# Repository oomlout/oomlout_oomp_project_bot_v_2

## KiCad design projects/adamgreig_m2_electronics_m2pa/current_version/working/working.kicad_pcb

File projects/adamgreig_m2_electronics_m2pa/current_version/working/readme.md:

# m2_electronics
 
## summary 
* id: adamgreig_m2_electronics_m2pa
* user: adamgreig
* name: m2_electronics
* board: m2pa
* repo: https://github.com/adamgreig/m2-electronics
* src_file_repo_kicad_pcb: m2pa/m2pa-instrument.kicad_pcb
* src_file_repo_kicad_pcb_link: https://github.com/adamgreig/m2-electronics/tree/master/m2pa/m2pa-instrument.kicad_pcb

* src_file_repo_sch: 
* src_file_repo_sch_link: https://github.com/adamgreig/m2-electronics/tree/master/
* full details link: https://github.com/oomlout/oomlout_oomp_project_bot_v_2/tree/main/projects/adamgreig_m2_electronics_m2pa/current_version/working  

## pcb  

[board (pdf)](working.pdf)  

## working_bom
| Id | Designator | Footprint | Quantity | Designation | Supplier and ref |  | None | 
| --- | --- | --- | --- | --- | --- | --- | --- | 
| 1 | C1 | C0402 | 1 | 10p |  |  | [''] | 
| 2 | C2,C7 | C0402 | 2 | 20p |  |  | [''] | 
| 3 | C3 | C0402 | 1 | 100p |  |  | [''] | 
| 4 | C4 | C0603 | 1 | 10n |  |  | [''] | 
| 5 | C5 | C0402 | 1 | 6p2 |  |  | [''] | 
| 6 | C6 | C1206 | 1 | 10Âµ |  |  | [''] | 
| 7 | D1,D2,D3 | R0402 | 3 | CGA0402MLC-12G |  |  | [''] | 
| 8 | IC1 | SOT89-3 | 1 | ADL5324 |  |  | [''] | 
| 9 | L1 | L0603 | 1 | 1n6 |  |  | [''] | 
| 10 | L2 | L0603 | 1 | 120n |  |  | [''] | 
| 11 | L3 | L0402 | 1 | 5n6 |  |  | [''] | 
| 12 | P1 | S02B-PASK-2 | 1 | CONN_01X02 |  |  | [''] | 
| 13 | P2,P3 | SMA-142-0701-801 | 2 | SMA |  |  | [''] | 
| 14 | R1 | R0402 | 1 | 2 |  |  | [''] | 
| 15 | G*** | cusf_logo_small | 1 | LOGO |  |  | [''] | 
| 16 | G*** | cusf_logo_full | 1 | LOGO |  |  | [''] |

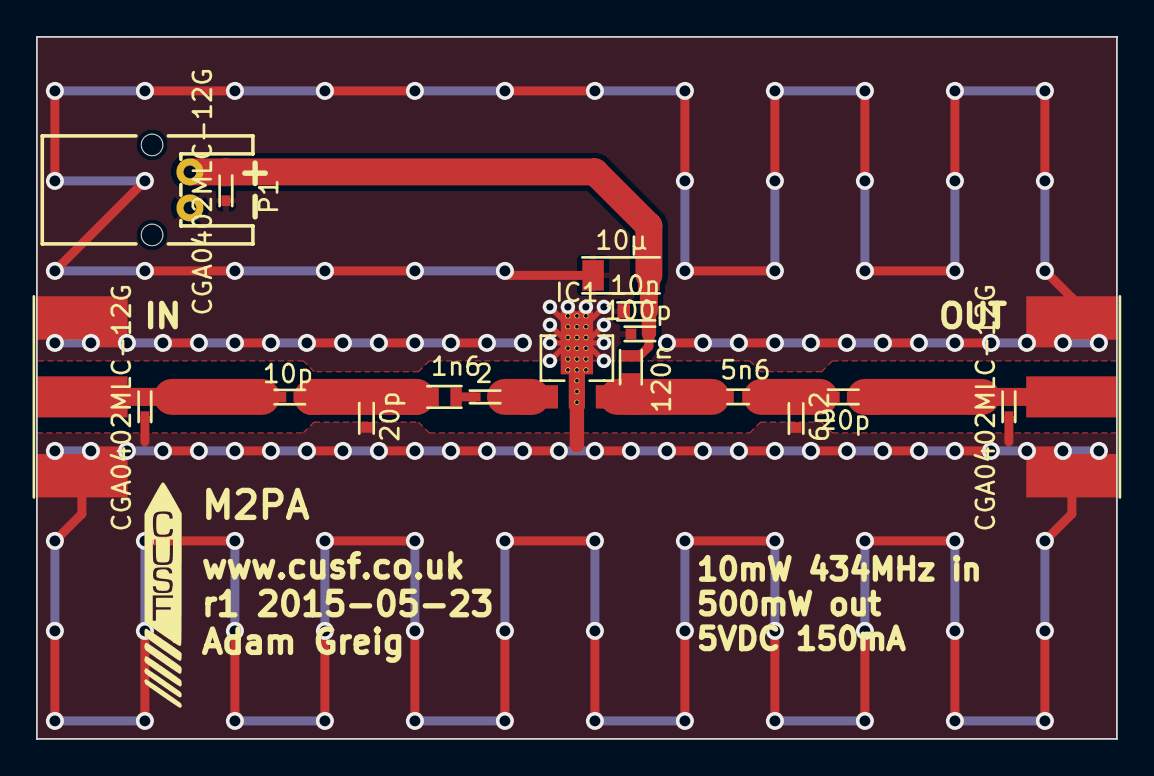
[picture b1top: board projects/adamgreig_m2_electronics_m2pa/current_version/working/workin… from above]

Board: 2 copper layers, 60.0 x 39.0 mm, 18 parts (0 on the bottom side), 9 nets.

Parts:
C1: 10p; C0402
C2, C7: 20p; C0402
C3: 100p; C0402
C4: 10n; C0603
C5: 6p2; C0402
C6: 10µ; C1206
D1, D2, D3: CGA0402MLC-12G; R0402
IC1: ADL5324; SOT89-3
L1: 1n6; L0603
L2: 120n; L0603
L3: 5n6; L0402
P1: CONN_01X02; S02B-PASK-2
P2, P3: SMA; SMA-142-0701-801
R1: 2; R0402

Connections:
+5V: C3.1, C4.1, C6.1, D3.1, L2.2, P1.2
GND: C2.1, C3.2, C4.2, C5.1, C6.2, D1.2, D2.2, D3.2, IC1.2, P1.1, P2.2, P2.3, P2.4, P2.5, P3.2, P3.3, P3.4, P3.5
unnamed: C1.1, C2.2, L1.2
unnamed: C1.2, D1.1, P2.1
unnamed: C5.2, C7.1, L3.1
unnamed: C7.2, D2.1, P3.1
unnamed: IC1.1, R1.1
unnamed: IC1.3, L2.1, L3.2
unnamed: L1.1, R1.2

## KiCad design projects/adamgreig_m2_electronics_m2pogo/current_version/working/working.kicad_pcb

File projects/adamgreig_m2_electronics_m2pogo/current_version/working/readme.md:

# m2_electronics
 
## summary 
* id: adamgreig_m2_electronics_m2pogo
* user: adamgreig
* name: m2_electronics
* board: m2pogo
* repo: https://github.com/adamgreig/m2-electronics
* src_file_repo_kicad_pcb: m2pogo/m2pogo.kicad_pcb
* src_file_repo_kicad_pcb_link: https://github.com/adamgreig/m2-electronics/tree/master/m2pogo/m2pogo.kicad_pcb

* src_file_repo_sch: m2pogo/m2pogo.sch
* src_file_repo_sch_link: https://github.com/adamgreig/m2-electronics/tree/master/m2pogo/m2pogo.sch
* full details link: https://github.com/oomlout/oomlout_oomp_project_bot_v_2/tree/main/projects/adamgreig_m2_electronics_m2pogo/current_version/working  

## schematic  
  
[schematic (pdf)](working_schematic.pdf) 

## pcb  

[board (pdf)](working.pdf)  

## working_bom
| Id | Designator | Footprint | Quantity | Designation | Supplier and ref |  | None | 
| --- | --- | --- | --- | --- | --- | --- | --- | 
| 1 | P3,P4,P5,P6 | POGO | 4 | CONN_1 |  |  | [''] | 
| 2 | P1,P2 | S02B-PASK-2 | 2 | CONN_2 |  |  | [''] | 
| 3 | X4,X3 | M3_MOUNT | 2 | MOUNT |  |  | [''] | 

## bom_schematic
| Ref | Qnty | Value | Cmp name | Footprint | Description | Vendor | DNP | 
| --- | --- | --- | --- | --- | --- | --- | --- | 
| P1, P2 | 2 | CONN_2 | CONN_2 | m2pogo:S02B-PASK-2 |  |  |  | 
| P3, P4, P5, P6 | 4 | CONN_1 | CONN_1 | m2pogo:POGO |  |  |  | 
| X1, X2 | 2 | HOUSING | PART |  |  |  |  | 
| X3, X4 | 2 | MOUNT | PART | m2pogo:M3_MOUNT |  |  |  |

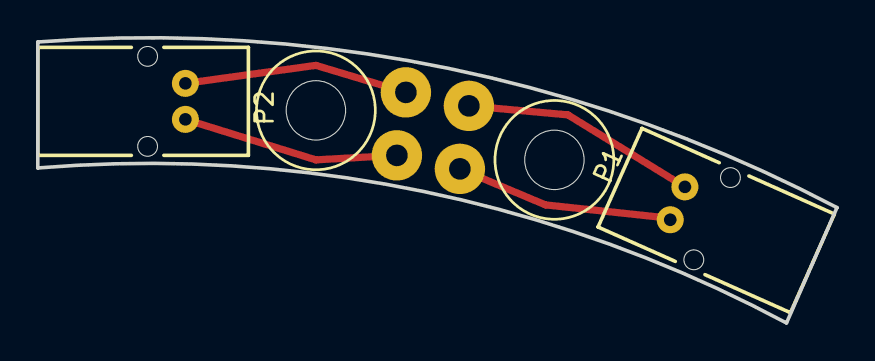
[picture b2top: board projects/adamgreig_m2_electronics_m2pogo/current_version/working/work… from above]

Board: 2 copper layers, 44.4 x 15.8 mm, 8 parts (0 on the bottom side), 4 nets.

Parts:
P1, P2: CONN_2; S02B-PASK-2
P3, P4, P5, P6: CONN_1; POGO
X3, X4: MOUNT; M3_MOUNT

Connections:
unnamed: P1.1, P4.1
unnamed: P1.2, P3.1
unnamed: P2.1, P6.1
unnamed: P2.2, P5.1

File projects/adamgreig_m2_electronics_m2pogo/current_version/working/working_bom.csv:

"Id";"Designator";"Footprint";"Quantity";"Designation";"Supplier and ref";
1;"P3,P4,P5,P6";"POGO";4;"CONN_1";;;
2;"P1,P2";"S02B-PASK-2";2;"CONN_2";;;
3;"X4,X3";"M3_MOUNT";2;"MOUNT";;;

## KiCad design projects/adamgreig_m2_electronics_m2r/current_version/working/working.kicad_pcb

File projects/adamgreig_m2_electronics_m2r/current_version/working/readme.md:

# m2_electronics
 
## summary 
* id: adamgreig_m2_electronics_m2r
* user: adamgreig
* name: m2_electronics
* board: m2r
* repo: https://github.com/adamgreig/m2-electronics
* src_file_repo_kicad_pcb: m2r/pcb_r2/m2r.kicad_pcb
* src_file_repo_kicad_pcb_link: https://github.com/adamgreig/m2-electronics/tree/master/m2r/pcb_r2/m2r.kicad_pcb

* src_file_repo_sch: m2r/pcb_r2/m2r.sch
* src_file_repo_sch_link: https://github.com/adamgreig/m2-electronics/tree/master/m2r/pcb_r2/m2r.sch
* full details link: https://github.com/oomlout/oomlout_oomp_project_bot_v_2/tree/main/projects/adamgreig_m2_electronics_m2r/current_version/working  

## pcb  

[board (pdf)](working.pdf)  

## working_bom
| Id | Designator | Footprint | Quantity | Designation | Supplier and ref |  | None | 
| --- | --- | --- | --- | --- | --- | --- | --- | 
| 1 | C1,C2,C3,C4,C5,C6,C11,C14,C15,C24,C25,C26,C27,C29,C30,C34 | C0603 | 16 | 100n |  |  | [''] | 
| 2 | C7,C8,C9,C10,C13 | C0603 | 5 | 2Âµ2 |  |  | [''] | 
| 3 | C12 | C0603 | 1 | 1n |  |  | [''] | 
| 4 | C23 | C0603 | 1 | 10Âµ |  |  | [''] | 
| 5 | C28 | C0603 | 1 | 1Âµ |  |  | [''] | 
| 6 | C35,C36 | C0603 | 2 | 15p |  |  | [''] | 
| 7 | D1,D2 | LED0603 | 2 | GRN |  |  | [''] | 
| 8 | D3,D4,D5,D6 | LED0603 | 4 | YELLOW |  |  | [''] | 
| 9 | D7,D8,D9,D10,D11,D12,D13 | R0402 | 7 | CGA0402MLC-12G |  |  | [''] | 
| 10 | IC1 | SOT223 | 1 | ADP3338 |  |  | [''] | 
| 11 | IC2 | MSOP8 | 1 | ADP3335 |  |  | [''] | 
| 12 | IC3,IC4,IC5 | SOIC8 | 3 | ADuM1201 |  |  | [''] | 
| 13 | IC6 | MTX2 | 1 | MTX2 |  |  | [''] | 
| 14 | IC8 | MAX-7Q | 1 | MAX-7Q |  |  | [''] | 
| 15 | IC10 | LQFP48 | 1 | STM32F303C |  |  | [''] | 
| 16 | P1,P8,P9 | S02B-PASK-2 | 3 | CONN_2 |  |  | [''] | 
| 17 | P2,P7 | SMA-142-0701-801 | 2 | SMA |  |  | [''] | 
| 18 | P3,P4,P5 | S04B-PASK-2 | 3 | CONN_4 |  |  | [''] | 
| 19 | P6 | FTSH-105-01-F-D-K | 1 | SWD |  |  | [''] | 
| 20 | Q1 | SOT-23 | 1 | Q_PMOS_GSD_PSV |  |  | [''] | 
| 21 | Q2 | SOT-23 | 1 | Q_NMOS_GSD_PSV |  |  | [''] | 
| 22 | R1,R3 | R0603 | 2 | 10k |  |  | [''] | 
| 23 | R2 | R0603 | 1 | 1k |  |  | [''] | 
| 24 | R4,R5,R7,R8,R9,R10,R11,R12,R13,R14,R15,R16 | R0603 | 12 | 100 |  |  | [''] | 
| 25 | R6 | R0603 | 1 | 10 |  |  | [''] | 
| 26 | SP1 | ABI-042-RC | 1 | SPEAKER |  |  | [''] | 
| 27 | TP1,TP2,TP4,TP7,TP11,TP12,TP13,TP14,TP15,TP16,TP17,TP18,TP19,TP20,TP21,TP22,TP23,TP24,TP25,TP26,TP27,TP28,TP29 | TESTPAD | 23 | TESTPAD |  |  | [''] | 
| 28 | X10 | XTAL50x32 | 1 | 8M |  |  | [''] | 
| 29 | X11,X12,X13,X14 | M3_MOUNT | 4 | M3 MOUNT |  |  | [''] | 
| 30 | G*** | cusf_logo_small | 1 | LOGO |  |  | [''] | 
| 31 | G*** | cusf_logo_full | 1 | LOGO |  |  | [''] |

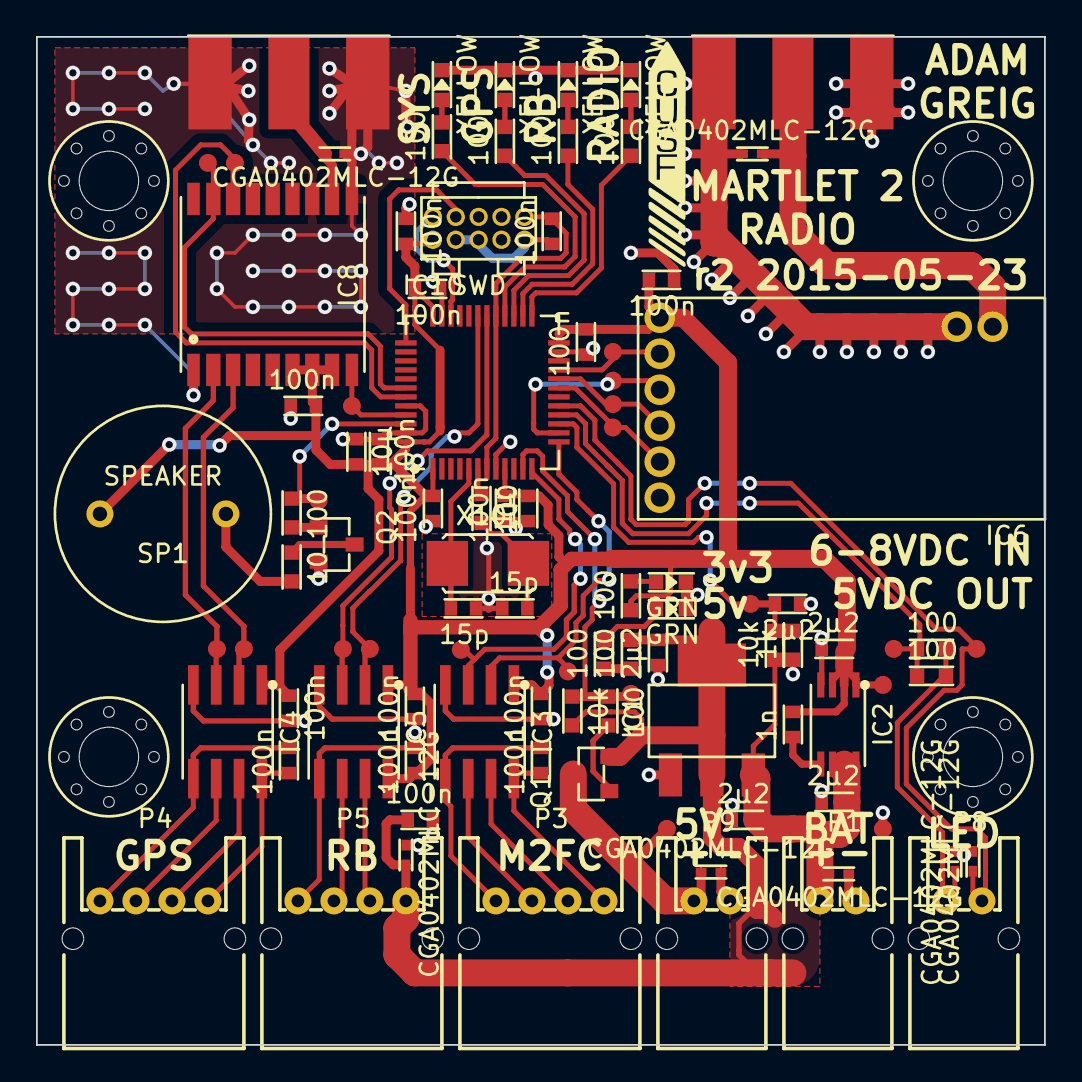
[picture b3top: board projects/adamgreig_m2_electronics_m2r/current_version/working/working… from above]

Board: 2 copper layers, 56.0 x 56.0 mm, 103 parts (0 on the bottom side), 58 nets.

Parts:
C1, C2, C3, C4, C5, C6, C11, C14, C15, C24, C25, C26, C27, C29, C30, C34: 100n; C0603
C7, C8, C9, C10, C13: 2µ2; C0603
C12: 1n; C0603
C23: 10µ; C0603
C28: 1µ; C0603
C35, C36: 15p; C0603
D1, D2: GRN; LED0603
D3, D4, D5, D6: YELLOW; LED0603
D7, D8, D9, D10, D11, D12, D13: CGA0402MLC-12G; R0402
IC1: ADP3338; SOT223
IC2: ADP3335; MSOP8
IC3, IC4, IC5: ADuM1201; SOIC8
IC6: MTX2
IC8: MAX-7Q
IC10: STM32F303C; LQFP48
P1, P8, P9: CONN_2; S02B-PASK-2
P2, P7: SMA; SMA-142-0701-801
P3, P4, P5: CONN_4; S04B-PASK-2
P6: SWD; FTSH-105-01-F-D-K
Q1: Q_PMOS_GSD_PSV; SOT-23
Q2: Q_NMOS_GSD_PSV; SOT-23
R1, R3: 10k; R0603
R2: 1k; R0603
R4, R5, R7, R8, R9, R10, R11, R12, R13, R14, R15, R16: 100; R0603
R6: 10; R0603
SP1: SPEAKER; ABI-042-RC
TP1, TP2, TP4, TP7, TP11, TP12, TP13, TP14, TP15, TP16, TP17, TP18, TP19, TP20, TP21, TP22, TP23, TP24, TP25, TP26, TP27, TP28, TP29: TESTPAD
X10: 8M; XTAL50x32
X11, X12, X13, X14: M3 MOUNT; M3_MOUNT

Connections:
5V_OUT: IC10.11, R3.2, R16.2, TP27.1
+3V3: C3.2, C5.2, C6.1, C8.1, C11.1, C12.1, C14.1, C15.1, C23.1, C24.1, C25.1, C26.1, C27.1, C28.1, C29.1, C30.1, IC2.1, IC2.2, IC2.3, IC3.1, IC4.1, IC5.1, IC5.8, IC6.3, IC8.6, IC8.7, IC8.8, IC10.1, IC10.9, IC10.24, IC10.36, IC10.48, P6.1, R8.2, SP1.1, TP1.1
+5V: C4.2, C10.1, D7.1, IC1.2, P5.1, Q1.2, R3.1, R9.1, TP2.1
+BATT: C7.1, C9.1, D8.1, IC1.3, IC2.6, IC2.7, IC2.8, P1.2, R1.2, TP11.1
BAT_MON: C13.1, IC10.15, R1.1, R2.1, TP13.1
BUZZER: IC10.46, R15.2, TP28.1
GND: C3.1, C4.1, C5.1, C6.2, C7.2, C8.2, C9.2, C10.2, C11.2, C13.2, C14.2, C15.2, C23.2, C24.2, C25.2, C26.2, C27.2, C28.2, C29.2, C30.2, C34.2, C35.2, C36.2, D1.2, D2.2, D3.2, D4.2, D5.2, D6.2, D7.2, D8.2, D9.2, D10.1, D11.1, D12.2, D13.1, IC1.1, IC2.4, IC3.4, IC4.4, IC5.4, IC5.5, IC6.2, IC6.8, IC8.1, IC8.10, IC8.12, IC10.8, IC10.23, IC10.35, IC10.44, IC10.47, P1.1, P2.2, P2.3, P2.4, P2.5, P5.4, P6.3, P6.5, P6.9, P7.2, P7.3, P7.4, P7.5, P9.1, Q2.2, R2.2, TP12.1
GPS_RESET: IC8.9, IC10.45, TP19.1
GPS_RX: IC4.2, IC8.3, TP4.1
GPS_SCL: IC8.17, IC10.42, TP20.1
GPS_SDA: IC8.16, IC10.43, TP21.1
GPS_TX: IC4.3, IC8.2, TP7.1
LED_1: IC10.25, R10.2
LED_2: IC10.26, R12.2
LED_3: IC10.27, R11.2
LED_4: IC10.28, R13.2
LED_A: IC10.16, R4.2, R5.2, TP18.1
LED_C: D11.2, IC10.17, P8.1, TP26.1
NTX2B_EN: IC6.4, IC10.21, TP22.1
NTX2B_P0: IC6.7, IC10.19, TP25.1
NTX2B_P1: IC6.6, IC10.20, TP24.1
NTX2B_TXD: IC6.5, IC10.14, TP23.1
unnamed: C1.1, IC4.5, P4.4
unnamed: C1.2, IC4.8, P4.1
unnamed: C2.1, IC3.5, P3.4
unnamed: C2.2, IC3.8, P3.1
unnamed: C12.2, IC2.5
unnamed: C35.1, IC10.5, X10.1
unnamed: C36.1, R14.1, X10.2
unnamed: D1.1, R8.1
unnamed: D2.1, R7.1
unnamed: D3.1, R10.1
unnamed: D4.1, R11.1
unnamed: D5.1, R12.1
unnamed: D6.1, R13.1
unnamed: D9.1, IC6.1, P7.1
unnamed: D10.2, P8.2, R4.1, R5.1
unnamed: D12.1, IC8.11, P2.1
unnamed: D13.2, P9.2, Q1.3, TP29.1
unnamed: IC3.6, P3.3
unnamed: IC3.7, P3.2
unnamed: IC4.6, P4.3
unnamed: IC4.7, P4.2
unnamed: IC5.6, P5.3
unnamed: IC5.7, P5.2
unnamed: IC10.6, R14.2
unnamed: Q1.1, R16.1
unnamed: Q2.1, R15.1
unnamed: Q2.3, R6.2
unnamed: R6.1, SP1.2
unnamed: R7.2, R9.2
RB_RX: IC5.3, IC10.30, TP14.1
RB_TX: IC5.2, IC10.31, TP15.1
SER_IN: IC3.2, IC10.13, TP17.1
SER_OUT: IC3.3, IC10.12, TP16.1
SWCLK: IC10.37, P6.4
SWDIO: IC10.34, P6.2
nRST: C34.1, IC10.7, IC10.29, P6.10

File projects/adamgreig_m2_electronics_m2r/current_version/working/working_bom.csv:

"Id";"Designator";"Footprint";"Quantity";"Designation";"Supplier and ref";
1;"C1,C2,C3,C4,C5,C6,C11,C14,C15,C24,C25,C26,C27,C29,C30,C34";"C0603";16;"100n";;;
2;"C7,C8,C9,C10,C13";"C0603";5;"2µ2";;;
3;"C12";"C0603";1;"1n";;;
4;"C23";"C0603";1;"10µ";;;
5;"C28";"C0603";1;"1µ";;;
6;"C35,C36";"C0603";2;"15p";;;
7;"D1,D2";"LED0603";2;"GRN";;;
8;"D3,D4,D5,D6";"LED0603";4;"YELLOW";;;
9;"D7,D8,D9,D10,D11,D12,D13";"R0402";7;"CGA0402MLC-12G";;;
10;"IC1";"SOT223";1;"ADP3338";;;
11;"IC2";"MSOP8";1;"ADP3335";;;
12;"IC3,IC4,IC5";"SOIC8";3;"ADuM1201";;;
13;"IC6";"MTX2";1;"MTX2";;;
14;"IC8";"MAX-7Q";1;"MAX-7Q";;;
15;"IC10";"LQFP48";1;"STM32F303C";;;
16;"P1,P8,P9";"S02B-PASK-2";3;"CONN_2";;;
17;"P2,P7";"SMA-142-0701-801";2;"SMA";;;
18;"P3,P4,P5";"S04B-PASK-2";3;"CONN_4";;;
19;"P6";"FTSH-105-01-F-D-K";1;"SWD";;;
20;"Q1";"SOT-23";1;"Q_PMOS_GSD_PSV";;;
21;"Q2";"SOT-23";1;"Q_NMOS_GSD_PSV";;;
22;"R1,R3";"R0603";2;"10k";;;
23;"R2";"R0603";1;"1k";;;
24;"R4,R5,R7,R8,R9,R10,R11,R12,R13,R14,R15,R16";"R0603";12;"100";;;
25;"R6";"R0603";1;"10";;;
26;"SP1";"ABI-042-RC";1;"SPEAKER";;;
27;"TP1,TP2,TP4,TP7,TP11,TP12,TP13,TP14,TP15,TP16,TP17,TP18,TP19,TP20,TP21,TP22,TP23,TP24,TP25,TP26,TP27,TP28,TP29";"TESTPAD";23;"TESTPAD";;;
28;"X10";"XTAL50x32";1;"8M";;;
29;"X11,X12,X13,X14";"M3_MOUNT";4;"M3 MOUNT";;;
30;"G***";"cusf_logo_small";1;"LOGO";;;
31;"G***";"cusf_logo_full";1;"LOGO";;;

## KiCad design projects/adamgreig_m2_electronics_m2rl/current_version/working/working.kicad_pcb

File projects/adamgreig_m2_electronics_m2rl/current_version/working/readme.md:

# m2_electronics
 
## summary 
* id: adamgreig_m2_electronics_m2rl
* user: adamgreig
* name: m2_electronics
* board: m2rl
* repo: https://github.com/adamgreig/m2-electronics
* src_file_repo_kicad_pcb: m2rl/pcb/m2rl.kicad_pcb
* src_file_repo_kicad_pcb_link: https://github.com/adamgreig/m2-electronics/tree/master/m2rl/pcb/m2rl.kicad_pcb

* src_file_repo_sch: m2rl/pcb/m2rl.sch
* src_file_repo_sch_link: https://github.com/adamgreig/m2-electronics/tree/master/m2rl/pcb/m2rl.sch
* full details link: https://github.com/oomlout/oomlout_oomp_project_bot_v_2/tree/main/projects/adamgreig_m2_electronics_m2rl/current_version/working  

## schematic  
  
[schematic (pdf)](working_schematic.pdf) 

## pcb  

[board (pdf)](working.pdf)  

## working_bom
| Id | Designator | Footprint | Quantity | Designation | Supplier and ref |  | None | 
| --- | --- | --- | --- | --- | --- | --- | --- | 
| 1 | C1,C7,C9 | C0603 | 3 | 10Âµ |  |  | [''] | 
| 2 | C2,C3,C5 | C0603 | 3 | 100n |  |  | [''] | 
| 3 | C4,C8 | C0603 | 2 | 2Âµ2 |  |  | [''] | 
| 4 | C6 | C0603 | 1 | 1n |  |  | [''] | 
| 5 | D1 | LED0603 | 1 | YELLOW |  |  | [''] | 
| 6 | D2 | R0402 | 1 | CGA0402MLC-12G |  |  | [''] | 
| 7 | D3,D4 | LED0603 | 2 | GRN |  |  | [''] | 
| 8 | IC1 | SOIC16W | 1 | ADuM5201 |  |  | [''] | 
| 9 | IC2 | MSOP8 | 1 | ADP3335 |  |  | [''] | 
| 10 | P1 | S02B-PASK-2 | 1 | CONN_01X02 |  |  | [''] | 
| 11 | P2 | S04B-PASK-2 | 1 | CONN_01X04 |  |  | [''] | 
| 12 | R1,R2,R3 | R0603 | 3 | 100 |  |  | [''] | 
| 13 | U1 | XBEE | 1 | XBEE |  |  | [''] | 
| 14 | M3_MOUNT,M3_MOUNT,M3_MOUNT,M3_MOUNT,M3_MOUNT,M3_MOUNT | M3_MOUNT | 6 | VAL** |  |  | [''] | 
| 15 | TP3,TP4,TP5 | TESTPAD | 3 | TESTPAD |  |  | [''] | 
| 16 | G*** | cusf_logo_small | 1 | LOGO |  |  | [''] | 

## bom_schematic
| Ref | Qnty | Value | Cmp name | Footprint | Description | Vendor | DNP | 
| --- | --- | --- | --- | --- | --- | --- | --- | 
| C1, C7, C9 | 3 | 10Âµ | C | m2rl:C0603 |  |  |  | 
| C2, C3, C5 | 3 | 100n | C | m2rl:C0603 |  |  |  | 
| C4, C8 | 2 | 2Âµ2 | C | m2rl:C0603 |  |  |  | 
| C6 | 1 | 1n | C | m2rl:C0603 |  |  |  | 
| D1 | 1 | YELLOW | LED | m2rl:LED0603 |  |  |  | 
| D2 | 1 | CGA0402MLC-12G | CGA0402MLC-12G | m2rl:R0402 |  |  |  | 
| D3, D4 | 2 | GRN | LED | m2rl:LED0603 |  |  |  | 
| IC1 | 1 | ADuM5201 | ADuM5201 | m2rl:SOIC16W |  |  |  | 
| IC2 | 1 | ADP3335 | ADP3335 | m2rl:MSOP8 |  |  |  | 
| P1 | 1 | CONN_01X02 | CONN_01X02 | m2rl:S02B-PASK-2 |  |  |  | 
| P2 | 1 | CONN_01X04 | CONN_01X04 | m2rl:S04B-PASK-2 |  |  |  | 
| R1, R2, R3 | 3 | 100 | R | m2rl:R0603 |  |  |  | 
| TP3, TP4, TP5 | 3 | TESTPAD | TESTPAD | m2rl:TESTPAD |  |  |  | 
| U1 | 1 | XBEE | XBEE | m2rl:XBEE |  |  |  |

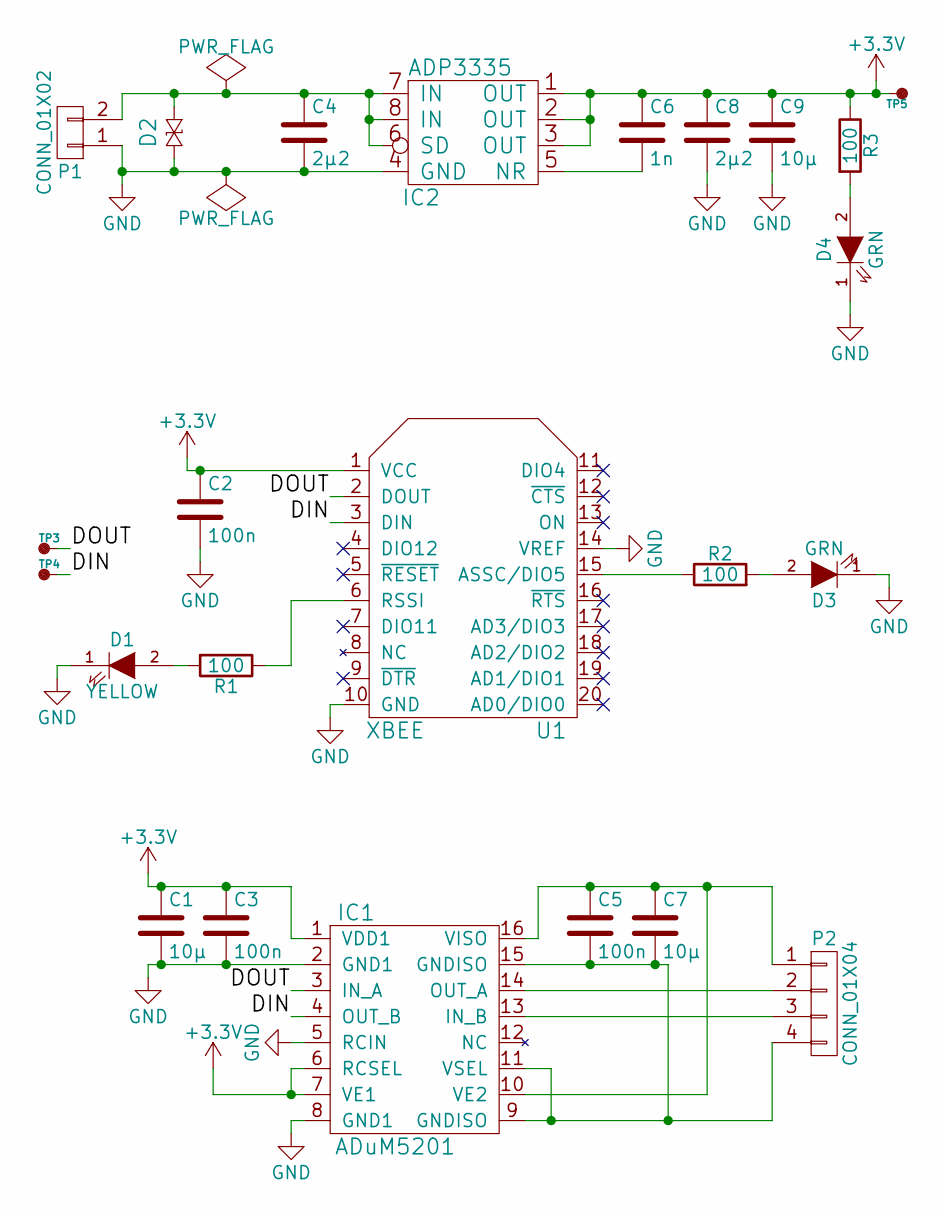
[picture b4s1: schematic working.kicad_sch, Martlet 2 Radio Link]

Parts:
C1, C7, C9: 10µ; C0603; Farnell 2211164
C2, C3, C5: 100n; C0603; Farnell 1759037
C4, C8: 2µ2; C0603; Farnell 2320817
C6: 1n; C0603; Farnell 1414605
D1: YELLOW; LED0603; Farnell 2290330
D2: CGA0402MLC-12G; R0402; Farnell 2368169
D3, D4: GRN; LED0603; Farnell 2290328
IC1: ADuM5201; SOIC16W; Farnell 2067773
IC2: ADP3335; MSOP8; Farnell 2067775
P1: CONN_01X02; S02B-PASK-2; Farnell 1830747
P2: CONN_01X04; S04B-PASK-2; Farnell 1830749
R1, R2, R3: 100; R0603; Farnell 2331989
TP3, TP4, TP5: TESTPAD
U1: XBEE; Farnell 1109732

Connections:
+3V3: C1.1, C2.1, C3.1, C6.1, C8.1, C9.1, IC1.1 (VDD1), IC1.6 (RCSEL), IC1.7 (VE1), IC2.1 (OUT), IC2.2 (OUT), IC2.3 (OUT), R3.1, TP5.1, U1.1 (VCC)
/DIN: IC1.4 (OUT_B), TP4.1, U1.3 (DIN)
/DOUT: IC1.3 (IN_A), TP3.1, U1.2 (DOUT)
GND: C1.2, C2.2, C3.2, C4.2, C8.2, C9.2, D1.1 (K), D2.2, D3.1 (K), D4.1 (K), IC1.2 (GND1), IC1.5 (RCIN), IC1.8 (GND1), IC2.4 (GND), P1.1, U1.10 (GND), U1.14 (VREF)
unnamed: C4.1, D2.1, IC2.6 (SD), IC2.7 (IN), IC2.8 (IN), P1.2
unnamed: C5.1, C7.1, IC1.10 (VE2), IC1.16 (VISO), P2.1
unnamed: C5.2, C7.2, IC1.9 (GNDISO), IC1.11 (VSEL), IC1.15 (GNDISO), P2.4
unnamed: C6.2, IC2.5 (NR)
unnamed: D1.2 (A), R1.2
unnamed: D3.2 (A), R2.2
unnamed: D4.2 (A), R3.2
unnamed: IC1.13 (IN_B), P2.3
unnamed: IC1.14 (OUT_A), P2.2
unnamed: R1.1, U1.6 (RSSI)
unnamed: R2.1, U1.15 (ASSC/DIO5)

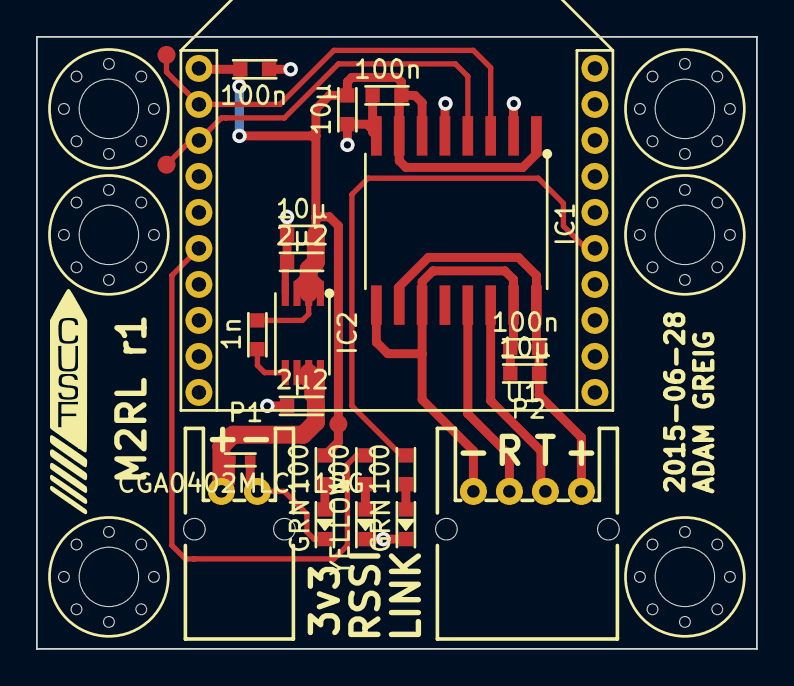
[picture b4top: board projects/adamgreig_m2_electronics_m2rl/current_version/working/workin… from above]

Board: 2 copper layers, 40.0 x 34.0 mm, 30 parts (0 on the bottom side), 15 nets.

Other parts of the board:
M3_MOUNT, M3_MOUNT#2, M3_MOUNT#3, M3_MOUNT#4, M3_MOUNT#5, M3_MOUNT#6: VAL**; M3_MOUNT

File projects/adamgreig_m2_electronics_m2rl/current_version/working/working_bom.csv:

"Id";"Designator";"Footprint";"Quantity";"Designation";"Supplier and ref";
1;"C1,C7,C9";"C0603";3;"10µ";;;
2;"C2,C3,C5";"C0603";3;"100n";;;
3;"C4,C8";"C0603";2;"2µ2";;;
4;"C6";"C0603";1;"1n";;;
5;"D1";"LED0603";1;"YELLOW";;;
6;"D2";"R0402";1;"CGA0402MLC-12G";;;
7;"D3,D4";"LED0603";2;"GRN";;;
8;"IC1";"SOIC16W";1;"ADuM5201";;;
9;"IC2";"MSOP8";1;"ADP3335";;;
10;"P1";"S02B-PASK-2";1;"CONN_01X02";;;
11;"P2";"S04B-PASK-2";1;"CONN_01X04";;;
12;"R1,R2,R3";"R0603";3;"100";;;
13;"U1";"XBEE";1;"XBEE";;;
14;"M3_MOUNT,M3_MOUNT,M3_MOUNT,M3_MOUNT,M3_MOUNT,M3_MOUNT";"M3_MOUNT";6;"VAL**";;;
15;"TP3,TP4,TP5";"TESTPAD";3;"TESTPAD";;;
16;"G***";"cusf_logo_small";1;"LOGO";;;
